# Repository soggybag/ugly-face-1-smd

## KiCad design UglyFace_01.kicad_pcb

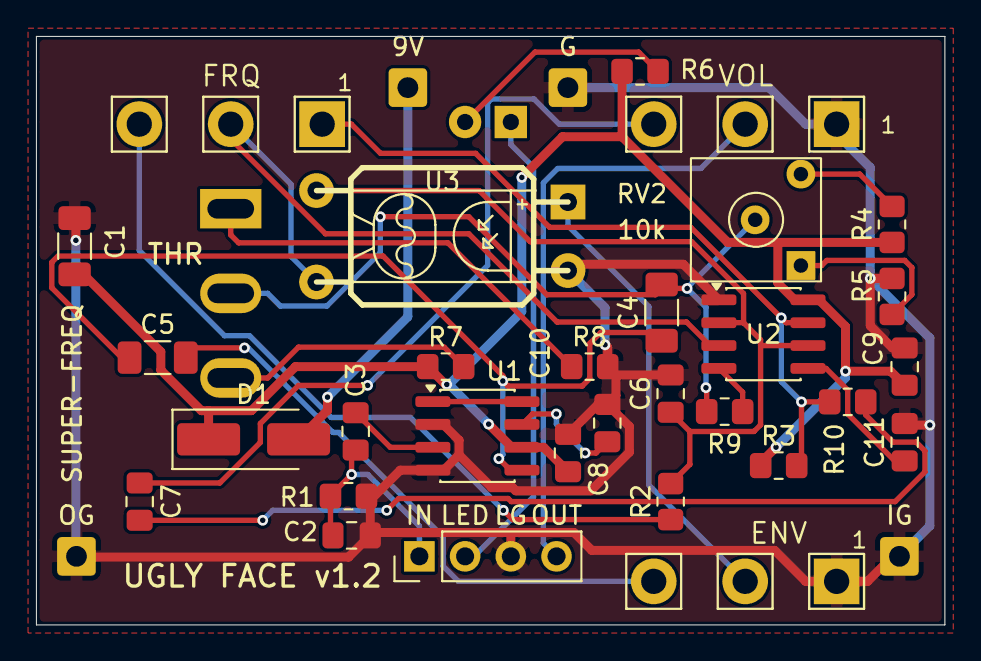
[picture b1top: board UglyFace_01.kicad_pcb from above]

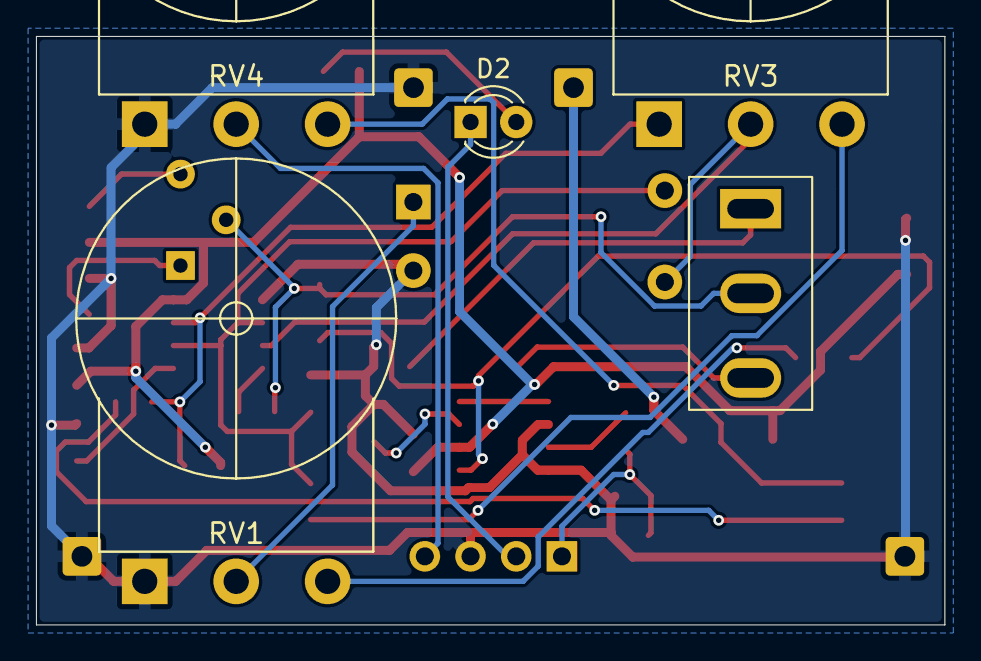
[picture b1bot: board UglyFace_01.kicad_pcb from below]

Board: 2 copper layers, 50.5 x 32.7 mm, 37 parts (3 on the bottom side), 26 nets.

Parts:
C1, C5: 22u; C_1206_3216Metric_Pad1.33x1.80mm_HandSolder
C2: 1n; C_0805_2012Metric_Pad1.18x1.45mm_HandSolder
C3, C6, C7, C8, C9: 100n; C_0805_2012Metric_Pad1.18x1.45mm_HandSolder
C4: 2.2u; C_1206_3216Metric_Pad1.33x1.80mm_HandSolder
C10: 10u; C_0805_2012Metric_Pad1.18x1.45mm_HandSolder
C11: 10n; C_0805_2012Metric_Pad1.18x1.45mm_HandSolder
D1: SS14; D_SMA_Handsoldering
D2: LED; LED_D3.0mm
ENC1: Hammond 1590B; Hammond_1590B
J1: 9V; SolderWire-0.5sqmm_1x01_D0.9mm_OD2.1mm
J2: 9V GND; SolderWire-0.5sqmm_1x01_D0.9mm_OD2.1mm
J3: IN/LED/LG/OUT; PinHeader_1x04_P2.54mm_Vertical
J4: IN GND; SolderWire-0.5sqmm_1x01_D0.9mm_OD2.1mm
J6: OUT GND; SolderWire-0.5sqmm_1x01_D0.9mm_OD2.1mm
R1: 1M; R_0805_2012Metric_Pad1.20x1.40mm_HandSolder
R2: 470; R_0805_2012Metric_Pad1.20x1.40mm_HandSolder
R3: 100k; R_0805_2012Metric_Pad1.20x1.40mm_HandSolder
R4, R9: 22k; R_0805_2012Metric_Pad1.20x1.40mm_HandSolder
R5, R6, R8, R10: 1k; R_0805_2012Metric_Pad1.20x1.40mm_HandSolder
R7: 2k2; R_0805_2012Metric_Pad1.20x1.40mm_HandSolder
RV1: B1k; Potentiometer_Alpha_16mm_Vertical
RV2: 10k; Potentiometer_Bourns_3362P_Vertical
RV3: C100k; Potentiometer_Alpha_16mm_Vertical
RV4: A100k; Potentiometer_Alpha_16mm_Vertical
SW1: THR; SW_Taiway_100_SPDT_PC
U1: LM386; SOIC-8_3.9x4.9mm_P1.27mm
U2: TLC555; SOIC-8_3.9x4.9mm_P1.27mm
U3: Vactrol; Vactrol_LED_LDR_DIY

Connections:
+9V: C1.1, C8.1, C9.1, D1.1 (K), R3.1, R4.1, R6.1, R7.1, U1.6 (V+), U2.8 (VCC)
/9V_IN: D1.2 (A), J1.1 (Pin_1_1)
/AMP_OUT: C4.1, C5.1, U1.5
/DISCH: R3.2, R10.1, RV3.1, U2.7 (DISCH)
/IN: C2.1, C3.1, J3.1, R1.1
/LED_K: D2.1 (K), J3.2
/OSC_SQ: RV3.2, U2.3 (OUT), U3.4 (R)
/OUT: J3.4, RV4.2
/RESET: R9.2, U2.4 (~RST)
/TIMING: C6.1, R2.2, U2.2 (TRIG), U2.6 (THRES), U3.3 (R)
/VACT_LED: RV1.2, U3.1 (A)
GND: C1.2, C2.2, C6.2, C8.2, C9.2, C10.2, C11.2, J2.1 (Pin_1_1), J3.3, J4.1 (Pin_1_1), J6.1 (Pin_1_1), R1.2, R5.2, R8.2, RV1.1, RV4.1, U1.2 (-), U1.4 (GND), U2.1 (GND), U3.2 (K)
unnamed: C5.2, RV1.3
unnamed: C7.1, R10.2
unnamed: C7.2, RV4.3
unnamed: D2.2 (A), R6.2
unnamed: R2.1, RV3.3
unnamed: R4.2, RV2.3
unnamed: R5.1, RV2.1
unnamed: R8.1, SW1.1
unnamed: C4.2, R9.1, RV2.2, SW1.2
unnamed: R7.2, SW1.3
unnamed: C3.2, U1.3 (+)
unnamed: C10.1, U1.7 (BYPASS)
unnamed: U1.1 (GAIN), U1.8 (GAIN)
unnamed: C11.1, U2.5 (CONT)
